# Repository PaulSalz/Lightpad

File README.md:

<div align="center">
<h1 align="center"><b>LightPad</b></h1>
DIY MIDI Controller to use with the Midi2LR Plugin

<picture>

</picture>
</div>
<br>

<picture>

</picture>

# Main features
- **[24x Interrupt-Driven Encoders](https://github.com/PaulSalz/lightpad/blob/main/Media/test_enc_led.jpg)**  
     - 3x8 RGB-illuminated Push-Button Encoders for all the main sliders, Lights, HSl, Details, ColorGrading, Effects...
- **[4x4 Button Matrix](https://github.com/PaulSalz/lightpad/blob/main/Media/top_view.jpg)**  
     - 16x RGB Buttons for easy Preset, Shortcut access
- **[Main Module](https://github.com/PaulSalz/lightpad/blob/main/Media/test_all.jpg)**  
     - 2x8 Buttons for switching Layers and often used features
- **[Media/ Culling Pad](https://github.com/PaulSalz/lightpad/blob/main/Media/side_view.jpg)**  
     - 8x RGB Buttons and an ANO Directional Navigation and Scroll Wheel to cull and navigate your library
- **[Force Feedback](https://github.com/PaulSalz/lightpad/blob/main/Media/test_all.jpg)**  
     - Integrated ERM Motor with DRV2605L for easy haptic effects 
- **[IR Remote Control](https://github.com/PaulSalz/lightpad/blob/main/Media/test_all.jpg)**  
     - Sometimes stepping back and cull from a distance helps me with culling
- **[Easy to print dual color case](https://www.rosa3d.pl/)**  
    - all printed from Rosa3D-Filaments PETG 
- **[Low/ High power mode](https://github.com/PaulSalz/lightpad/blob/main/Hardware/LightPad_BOM.html)**  
    - Full brightness gets unlocked with a external 5V source, and a mechanical switch on the main controller to prevent brown outs
- **[Animations]()**  
    - Idle animation
    - Button/ Encoder Effects
    - Backside illumination
- **[EL-Facts](https://github.com/PaulSalz/lightpad/blob/main/Media/usecase.jpg)**
    - Teensy 4.1 based
    - resettable fuses for both power inputs
    - RT1985N-A Protection IC for Softstart (needs some work)
    - I²C Level Shift 
    - Dual 74HC2G34 Buffer Gate for the LED's (using DMA)
    - expansion header for a Touch SPI Screen
    - all inputs connected through MCP23017 I/O expanders
  
<br>
<div align="center">
     
<picture>

</picture>
<picture>

</picture>
<picture>

</picture>
     
</div>
<br>

## TO-DO
  - fix all the bugs that occurred during assembly
  - rewrite the code so everything can be configured on the fly without reflashing
  - ...

## Background
- In the past I used a Behringer X-Touch mini for editing with Lightroom Classic and although this worked somewhat great enough to convince colleagues to also get one I wanted more, having to constantly switch layers, modes and remembering all of them to find the right settings annoyed me and gave me the motivation for this. 
  There are other great options out there but I wanted something without proprietary software that maybe gets bricked in the future. and i wanted something fancy, something completly over the top, do you need that many LED's? hell no..  But they definitely help a lot with remembering all the functions and look awesome.

## Disclaimer
- This is a first try on a DIY Midi controller that was created roughly in a span of a month from idea to actually getting used.  
- There will be and there are bugs, for example part of the pcb's need a bit of rework and changes to work out of the box.

<br>
<div align="center">
     
<picture>

</picture>
<picture>

</picture>
     
</div>
<br>

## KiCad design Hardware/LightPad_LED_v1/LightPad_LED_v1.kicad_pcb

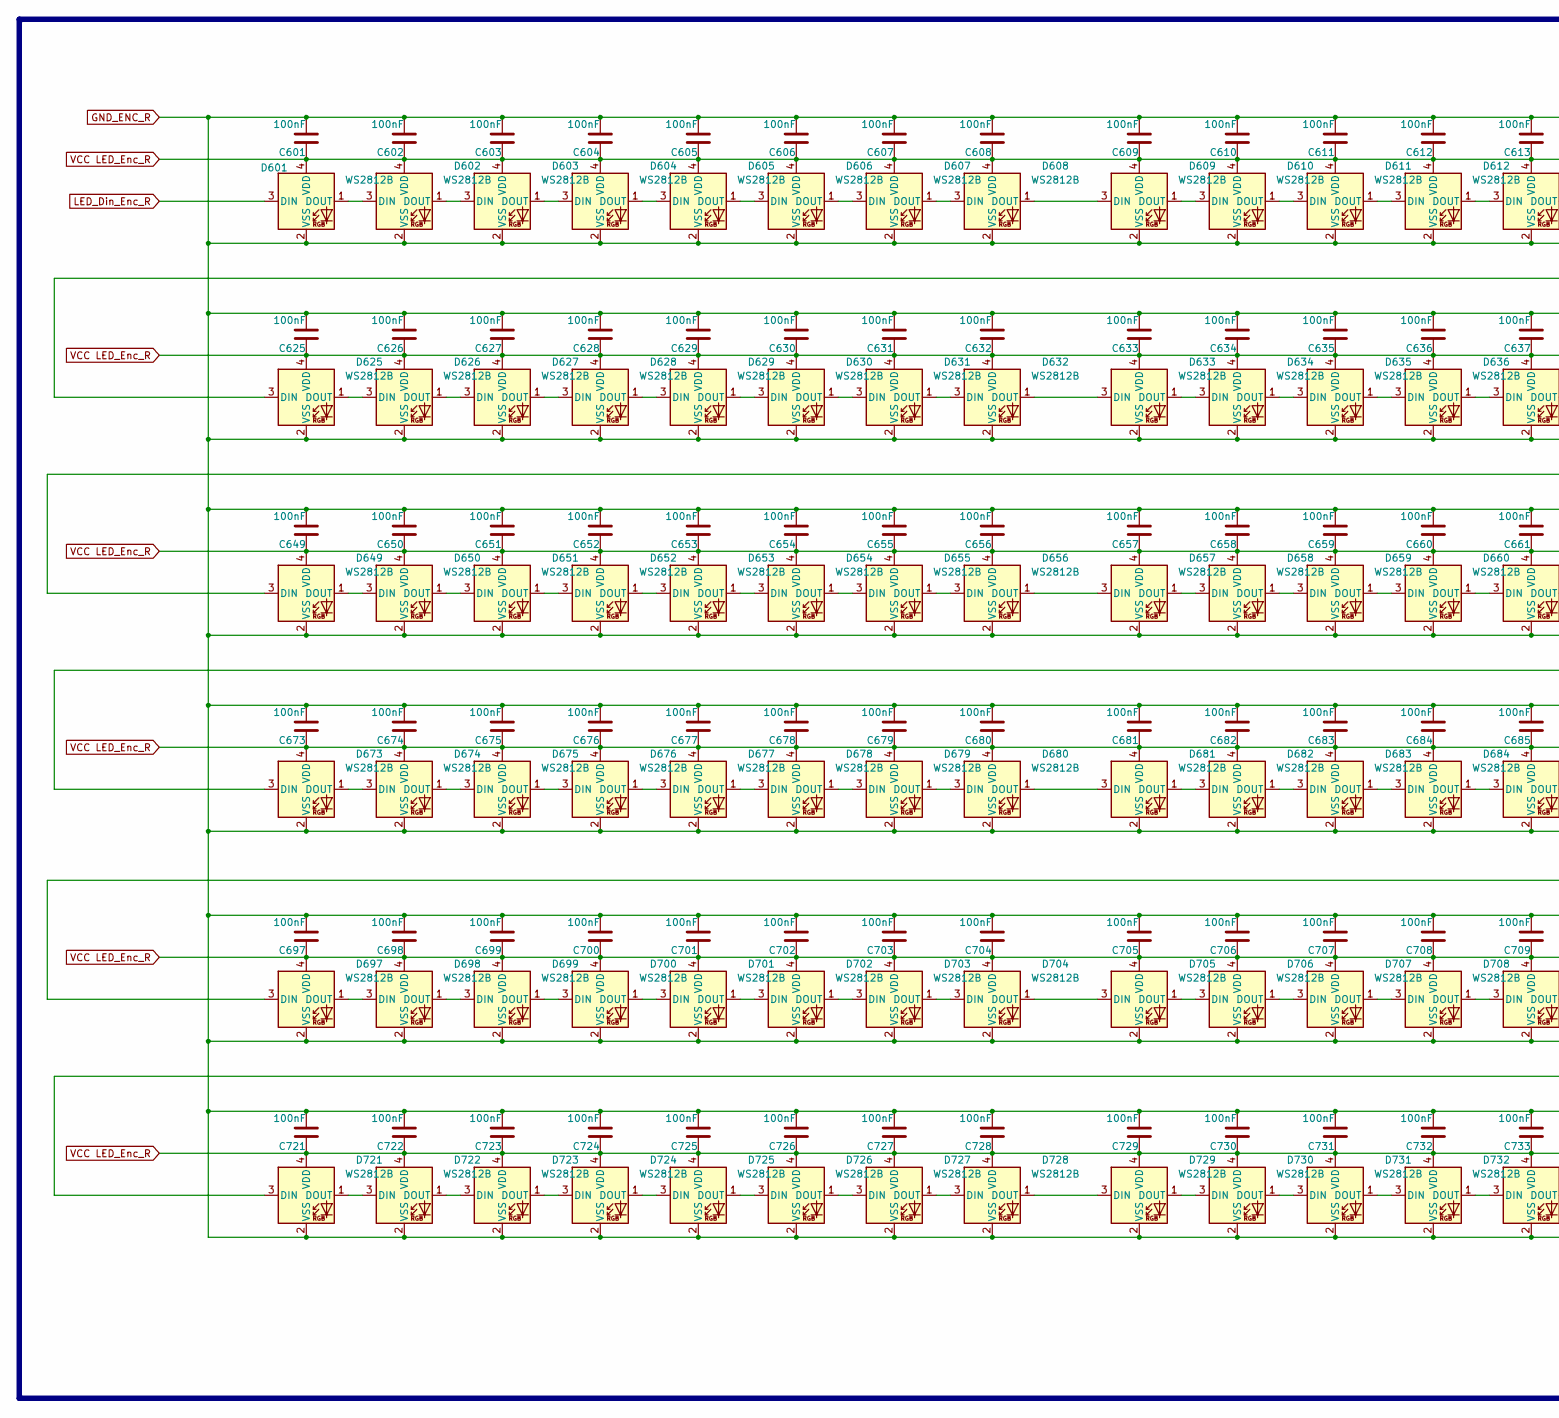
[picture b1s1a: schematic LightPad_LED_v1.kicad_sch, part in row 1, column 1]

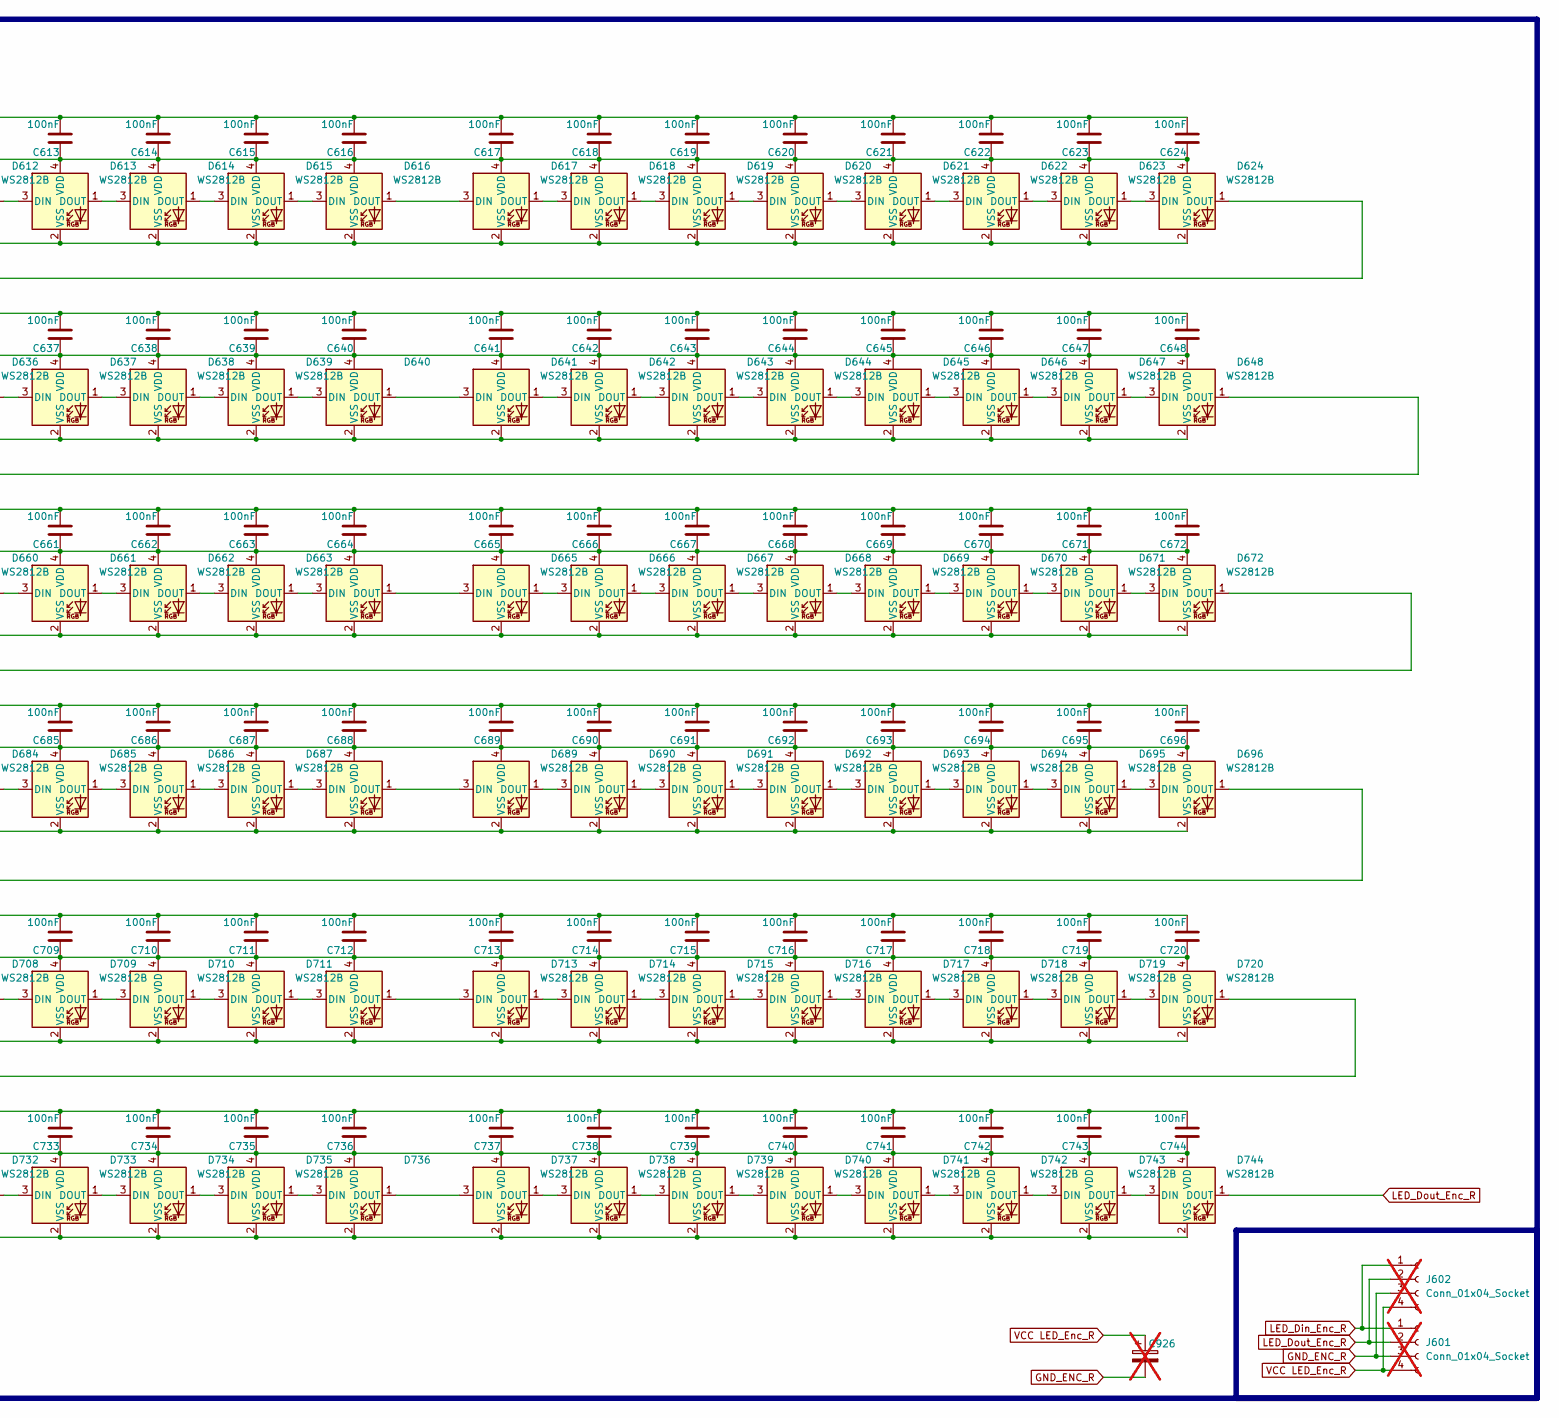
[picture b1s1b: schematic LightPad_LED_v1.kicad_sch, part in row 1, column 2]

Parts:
C601, C602, C603, C604, C605, C606, C607, C608, C609, C610, C611, C612, C613, C614, C615, C616, C617, C618, C619, C620, C621, C622, C623, C624, C625, C626, C627, C628, C629, C630, C631, C632, C633, C634, C635, C636, C637, C638, C639, C640, C641, C642, C643, C644, C645, C646, C647, C648, C649, C650, C651, C652, C653, C654, C655, C656, C657, C658, C659, C660, C661, C662, C663, C664, C665, C666, C667, C668, C669, C670, C671, C672, C673, C674, C675, C676, C677, C678, C679, C680, C681, C682, C683, C684, C685, C686, C687, C688, C689, C690, C691, C692, C693, C694, C695, C696, C697, C698, C699, C700, C701, C702, C703, C704, C705, C706, C707, C708, C709, C710, C711, C712, C713, C714, C715, C716, C717, C718, C719, C720, C721, C722, C723, C724, C725, C726, C727, C728, C729, C730, C731, C732, C733, C734, C735, C736, C737, C738, C739, C740, C741, C742, C743, C744: 100nF; C_0603_1608Metric; LCSC C24452
C926: APXE100ARA471MJ80G; C_Radial_D6.3mm_H5.0mm_P2.50mm; not fitted
D601, D602, D603, D604, D605, D606, D607, D608, D609, D610, D611, D612, D613, D614, D615, D616, D617, D618, D619, D620, D621, D622, D623, D624, D625, D626, D627, D628, D629, D630, D631, D632, D633, D634, D635, D636, D637, D638, D639, D640, D641, D642, D643, D644, D645, D646, D647, D648, D649, D650, D651, D652, D653, D654, D655, D656, D657, D658, D659, D660, D661, D662, D663, D664, D665, D666, D667, D668, D669, D670, D671, D672, D673, D674, D675, D676, D677, D678, D679, D680, D681, D682, D683, D684, D685, D686, D687, D688, D689, D690, D691, D692, D693, D694, D695, D696, D697, D698, D699, D700, D701, D702, D703, D704, D705, D706, D707, D708, D709, D710, D711, D712, D713, D714, D715, D716, D717, D718, D719, D720, D721, D722, D723, D724, D725, D726, D727, D728, D729, D730, D731, D732, D733, D734, D735, D736, D737, D738, D739, D740, D741, D742, D743, D744: WS2812B; LED_WS2812B-2020_PLCC4_2.0x2.0mm; LCSC C965555
J601, J602: Conn_01x04_Socket; PinSocket_1x04_P2.54mm_Vertical; not fitted

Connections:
GND_ENC_R: C601.1, C602.1, C603.1, C604.1, C605.1, C606.1, C607.1, C608.1, C609.1, C610.1, C611.1, C612.1, C613.1, C614.1, C615.1, C616.1, C617.1, C618.1, C619.1, C620.1, C621.1, C622.1, C623.1, C624.1, C625.1, C626.1, C627.1, C628.1, C629.1, C630.1, C631.1, C632.1, C633.1, C634.1, C635.1, C636.1, C637.1, C638.1, C639.1, C640.1, C641.1, C642.1, C643.1, C644.1, C645.1, C646.1, C647.1, C648.1, C649.1, C650.1, C651.1, C652.1, C653.1, C654.1, C655.1, C656.1, C657.1, C658.1, C659.1, C660.1, C661.1, C662.1, C663.1, C664.1, C665.1, C666.1, C667.1, C668.1, C669.1, C670.1, C671.1, C672.1, C673.1, C674.1, C675.1, C676.1, C677.1, C678.1, C679.1, C680.1, C681.1, C682.1, C683.1, C684.1, C685.1, C686.1, C687.1, C688.1, C689.1, C690.1, C691.1, C692.1, C693.1, C694.1, C695.1, C696.1, C697.1, C698.1, C699.1, C700.1, C701.1, C702.1, C703.1, C704.1, C705.1, C706.1, C707.1, C708.1, C709.1, C710.1, C711.1, C712.1, C713.1, C714.1, C715.1, C716.1, C717.1, C718.1, C719.1, C720.1, C721.1, C722.1, C723.1, C724.1, C725.1, C726.1, C727.1, C728.1, C729.1, C730.1, C731.1, C732.1, C733.1, C734.1, C735.1, C736.1, C737.1, C738.1, C739.1, C740.1, C741.1, C742.1, C743.1, C744.1, C926.2, D601.2 (VSS), D602.2 (VSS), D603.2 (VSS), D604.2 (VSS), D605.2 (VSS), D606.2 (VSS), D607.2 (VSS), D608.2 (VSS), D609.2 (VSS), D610.2 (VSS), D611.2 (VSS), D612.2 (VSS), D613.2 (VSS), D614.2 (VSS), D615.2 (VSS), D616.2 (VSS), D617.2 (VSS), D618.2 (VSS), D619.2 (VSS), D620.2 (VSS), D621.2 (VSS), D622.2 (VSS), D623.2 (VSS), D624.2 (VSS), D625.2 (VSS), D626.2 (VSS), D627.2 (VSS), D628.2 (VSS), D629.2 (VSS), D630.2 (VSS), D631.2 (VSS), D632.2 (VSS), D633.2 (VSS), D634.2 (VSS), D635.2 (VSS), D636.2 (VSS), D637.2 (VSS), D638.2 (VSS), D639.2 (VSS), D640.2 (VSS), D641.2 (VSS), D642.2 (VSS), D643.2 (VSS), D644.2 (VSS), D645.2 (VSS), D646.2 (VSS), D647.2 (VSS), D648.2 (VSS), D649.2 (VSS), D650.2 (VSS), D651.2 (VSS), D652.2 (VSS), D653.2 (VSS), D654.2 (VSS), D655.2 (VSS), D656.2 (VSS), D657.2 (VSS), D658.2 (VSS), D659.2 (VSS), D660.2 (VSS), D661.2 (VSS), D662.2 (VSS), D663.2 (VSS), D664.2 (VSS), D665.2 (VSS), D666.2 (VSS), D667.2 (VSS), D668.2 (VSS), D669.2 (VSS), D670.2 (VSS), D671.2 (VSS), D672.2 (VSS), D673.2 (VSS), D674.2 (VSS), D675.2 (VSS), D676.2 (VSS), D677.2 (VSS), D678.2 (VSS), D679.2 (VSS), D680.2 (VSS), D681.2 (VSS), D682.2 (VSS), D683.2 (VSS), D684.2 (VSS), D685.2 (VSS), D686.2 (VSS), D687.2 (VSS), D688.2 (VSS), D689.2 (VSS), D690.2 (VSS), D691.2 (VSS), D692.2 (VSS), D693.2 (VSS), D694.2 (VSS), D695.2 (VSS), D696.2 (VSS), D697.2 (VSS), D698.2 (VSS), D699.2 (VSS), D700.2 (VSS), D701.2 (VSS), D702.2 (VSS), D703.2 (VSS), D704.2 (VSS), D705.2 (VSS), D706.2 (VSS), D707.2 (VSS), D708.2 (VSS), D709.2 (VSS), D710.2 (VSS), D711.2 (VSS), D712.2 (VSS), D713.2 (VSS), D714.2 (VSS), D715.2 (VSS), D716.2 (VSS), D717.2 (VSS), D718.2 (VSS), D719.2 (VSS), D720.2 (VSS), D721.2 (VSS), D722.2 (VSS), D723.2 (VSS), D724.2 (VSS), D725.2 (VSS), D726.2 (VSS), D727.2 (VSS), D728.2 (VSS), D729.2 (VSS), D730.2 (VSS), D731.2 (VSS), D732.2 (VSS), D733.2 (VSS), D734.2 (VSS), D735.2 (VSS), D736.2 (VSS), D737.2 (VSS), D738.2 (VSS), D739.2 (VSS), D740.2 (VSS), D741.2 (VSS), D742.2 (VSS), D743.2 (VSS), D744.2 (VSS), J601.3, J602.3
LED_Din_Enc_R: D601.3 (DIN), J601.1, J602.1
LED_Dout_Enc_R: D744.1 (DOUT), J601.2, J602.2
unnamed: D601.1 (DOUT), D602.3 (DIN)
unnamed: D602.1 (DOUT), D603.3 (DIN)
unnamed: D603.1 (DOUT), D604.3 (DIN)
unnamed: D604.1 (DOUT), D605.3 (DIN)
unnamed: D605.1 (DOUT), D606.3 (DIN)
unnamed: D606.1 (DOUT), D607.3 (DIN)
unnamed: D607.1 (DOUT), D608.3 (DIN)
unnamed: D608.1 (DOUT), D609.3 (DIN)
unnamed: D609.1 (DOUT), D610.3 (DIN)
unnamed: D610.1 (DOUT), D611.3 (DIN)
unnamed: D611.1 (DOUT), D612.3 (DIN)
unnamed: D612.1 (DOUT), D613.3 (DIN)
unnamed: D613.1 (DOUT), D614.3 (DIN)
unnamed: D614.1 (DOUT), D615.3 (DIN)
unnamed: D615.1 (DOUT), D616.3 (DIN)
unnamed: D616.1 (DOUT), D617.3 (DIN)
unnamed: D617.1 (DOUT), D618.3 (DIN)
unnamed: D618.1 (DOUT), D619.3 (DIN)
unnamed: D619.1 (DOUT), D620.3 (DIN)
unnamed: D620.1 (DOUT), D621.3 (DIN)
unnamed: D621.1 (DOUT), D622.3 (DIN)
unnamed: D622.1 (DOUT), D623.3 (DIN)
unnamed: D623.1 (DOUT), D624.3 (DIN)
unnamed: D624.1 (DOUT), D625.3 (DIN)
unnamed: D625.1 (DOUT), D626.3 (DIN)
unnamed: D626.1 (DOUT), D627.3 (DIN)
unnamed: D627.1 (DOUT), D628.3 (DIN)
unnamed: D628.1 (DOUT), D629.3 (DIN)
unnamed: D629.1 (DOUT), D630.3 (DIN)
unnamed: D630.1 (DOUT), D631.3 (DIN)
unnamed: D631.1 (DOUT), D632.3 (DIN)
unnamed: D632.1 (DOUT), D633.3 (DIN)
unnamed: D633.1 (DOUT), D634.3 (DIN)
unnamed: D634.1 (DOUT), D635.3 (DIN)
unnamed: D635.1 (DOUT), D636.3 (DIN)
unnamed: D636.1 (DOUT), D637.3 (DIN)
unnamed: D637.1 (DOUT), D638.3 (DIN)
unnamed: D638.1 (DOUT), D639.3 (DIN)
unnamed: D639.1 (DOUT), D640.3 (DIN)
unnamed: D640.1 (DOUT), D641.3 (DIN)
unnamed: D641.1 (DOUT), D642.3 (DIN)
unnamed: D642.1 (DOUT), D643.3 (DIN)
unnamed: D643.1 (DOUT), D644.3 (DIN)
unnamed: D644.1 (DOUT), D645.3 (DIN)
unnamed: D645.1 (DOUT), D646.3 (DIN)
unnamed: D646.1 (DOUT), D647.3 (DIN)
unnamed: D647.1 (DOUT), D648.3 (DIN)
unnamed: D648.1 (DOUT), D649.3 (DIN)
unnamed: D649.1 (DOUT), D650.3 (DIN)
unnamed: D650.1 (DOUT), D651.3 (DIN)
unnamed: D651.1 (DOUT), D652.3 (DIN)
unnamed: D652.1 (DOUT), D653.3 (DIN)
unnamed: D653.1 (DOUT), D654.3 (DIN)
unnamed: D654.1 (DOUT), D655.3 (DIN)
unnamed: D655.1 (DOUT), D656.3 (DIN)
unnamed: D656.1 (DOUT), D657.3 (DIN)
unnamed: D657.1 (DOUT), D658.3 (DIN)
unnamed: D658.1 (DOUT), D659.3 (DIN)
unnamed: D659.1 (DOUT), D660.3 (DIN)
unnamed: D660.1 (DOUT), D661.3 (DIN)
unnamed: D661.1 (DOUT), D662.3 (DIN)
unnamed: D662.1 (DOUT), D663.3 (DIN)
unnamed: D663.1 (DOUT), D664.3 (DIN)
unnamed: D664.1 (DOUT), D665.3 (DIN)
unnamed: D665.1 (DOUT), D666.3 (DIN)
unnamed: D666.1 (DOUT), D667.3 (DIN)
unnamed: D667.1 (DOUT), D668.3 (DIN)
unnamed: D668.1 (DOUT), D669.3 (DIN)
unnamed: D669.1 (DOUT), D670.3 (DIN)
unnamed: D670.1 (DOUT), D671.3 (DIN)
unnamed: D671.1 (DOUT), D672.3 (DIN)
unnamed: D672.1 (DOUT), D673.3 (DIN)
unnamed: D673.1 (DOUT), D674.3 (DIN)
unnamed: D674.1 (DOUT), D675.3 (DIN)
unnamed: D675.1 (DOUT), D676.3 (DIN)
unnamed: D676.1 (DOUT), D677.3 (DIN)
unnamed: D677.1 (DOUT), D678.3 (DIN)
unnamed: D678.1 (DOUT), D679.3 (DIN)
unnamed: D679.1 (DOUT), D680.3 (DIN)
unnamed: D680.1 (DOUT), D681.3 (DIN)
unnamed: D681.1 (DOUT), D682.3 (DIN)
unnamed: D682.1 (DOUT), D683.3 (DIN)
unnamed: D683.1 (DOUT), D684.3 (DIN)
unnamed: D684.1 (DOUT), D685.3 (DIN)
unnamed: D685.1 (DOUT), D686.3 (DIN)
unnamed: D686.1 (DOUT), D687.3 (DIN)
unnamed: D687.1 (DOUT), D688.3 (DIN)
unnamed: D688.1 (DOUT), D689.3 (DIN)
unnamed: D689.1 (DOUT), D690.3 (DIN)
unnamed: D690.1 (DOUT), D691.3 (DIN)
unnamed: D691.1 (DOUT), D692.3 (DIN)
unnamed: D692.1 (DOUT), D693.3 (DIN)
unnamed: D693.1 (DOUT), D694.3 (DIN)
unnamed: D694.1 (DOUT), D695.3 (DIN)
unnamed: D695.1 (DOUT), D696.3 (DIN)
unnamed: D696.1 (DOUT), D697.3 (DIN)
unnamed: D697.1 (DOUT), D698.3 (DIN)
unnamed: D698.1 (DOUT), D699.3 (DIN)
unnamed: D699.1 (DOUT), D700.3 (DIN)
unnamed: D700.1 (DOUT), D701.3 (DIN)
unnamed: D701.1 (DOUT), D702.3 (DIN)
unnamed: D702.1 (DOUT), D703.3 (DIN)
unnamed: D703.1 (DOUT), D704.3 (DIN)
unnamed: D704.1 (DOUT), D705.3 (DIN)
unnamed: D705.1 (DOUT), D706.3 (DIN)
unnamed: D706.1 (DOUT), D707.3 (DIN)
unnamed: D707.1 (DOUT), D708.3 (DIN)
unnamed: D708.1 (DOUT), D709.3 (DIN)
unnamed: D709.1 (DOUT), D710.3 (DIN)
unnamed: D710.1 (DOUT), D711.3 (DIN)
unnamed: D711.1 (DOUT), D712.3 (DIN)
unnamed: D712.1 (DOUT), D713.3 (DIN)
unnamed: D713.1 (DOUT), D714.3 (DIN)
unnamed: D714.1 (DOUT), D715.3 (DIN)
unnamed: D715.1 (DOUT), D716.3 (DIN)
unnamed: D716.1 (DOUT), D717.3 (DIN)
unnamed: D717.1 (DOUT), D718.3 (DIN)
unnamed: D718.1 (DOUT), D719.3 (DIN)
unnamed: D719.1 (DOUT), D720.3 (DIN)
unnamed: D720.1 (DOUT), D721.3 (DIN)
unnamed: D721.1 (DOUT), D722.3 (DIN)
unnamed: D722.1 (DOUT), D723.3 (DIN)
unnamed: D723.1 (DOUT), D724.3 (DIN)
unnamed: D724.1 (DOUT), D725.3 (DIN)
unnamed: D725.1 (DOUT), D726.3 (DIN)
unnamed: D726.1 (DOUT), D727.3 (DIN)
unnamed: D727.1 (DOUT), D728.3 (DIN)
unnamed: D728.1 (DOUT), D729.3 (DIN)
unnamed: D729.1 (DOUT), D730.3 (DIN)
unnamed: D730.1 (DOUT), D731.3 (DIN)
unnamed: D731.1 (DOUT), D732.3 (DIN)
unnamed: D732.1 (DOUT), D733.3 (DIN)
unnamed: D733.1 (DOUT), D734.3 (DIN)
unnamed: D734.1 (DOUT), D735.3 (DIN)
unnamed: D735.1 (DOUT), D736.3 (DIN)
unnamed: D736.1 (DOUT), D737.3 (DIN)
unnamed: D737.1 (DOUT), D738.3 (DIN)
unnamed: D738.1 (DOUT), D739.3 (DIN)
unnamed: D739.1 (DOUT), D740.3 (DIN)
unnamed: D740.1 (DOUT), D741.3 (DIN)
unnamed: D741.1 (DOUT), D742.3 (DIN)
unnamed: D742.1 (DOUT), D743.3 (DIN)
unnamed: D743.1 (DOUT), D744.3 (DIN)
VCC LED_Enc_R: C601.2, C602.2, C603.2, C604.2, C605.2, C606.2, C607.2, C608.2, C609.2, C610.2, C611.2, C612.2, C613.2, C614.2, C615.2, C616.2, C617.2, C618.2, C619.2, C620.2, C621.2, C622.2, C623.2, C624.2, C625.2, C626.2, C627.2, C628.2, C629.2, C630.2, C631.2, C632.2, C633.2, C634.2, C635.2, C636.2, C637.2, C638.2, C639.2, C640.2, C641.2, C642.2, C643.2, C644.2, C645.2, C646.2, C647.2, C648.2, C649.2, C650.2, C651.2, C652.2, C653.2, C654.2, C655.2, C656.2, C657.2, C658.2, C659.2, C660.2, C661.2, C662.2, C663.2, C664.2, C665.2, C666.2, C667.2, C668.2, C669.2, C670.2, C671.2, C672.2, C673.2, C674.2, C675.2, C676.2, C677.2, C678.2, C679.2, C680.2, C681.2, C682.2, C683.2, C684.2, C685.2, C686.2, C687.2, C688.2, C689.2, C690.2, C691.2, C692.2, C693.2, C694.2, C695.2, C696.2, C697.2, C698.2, C699.2, C700.2, C701.2, C702.2, C703.2, C704.2, C705.2, C706.2, C707.2, C708.2, C709.2, C710.2, C711.2, C712.2, C713.2, C714.2, C715.2, C716.2, C717.2, C718.2, C719.2, C720.2, C721.2, C722.2, C723.2, C724.2, C725.2, C726.2, C727.2, C728.2, C729.2, C730.2, C731.2, C732.2, C733.2, C734.2, C735.2, C736.2, C737.2, C738.2, C739.2, C740.2, C741.2, C742.2, C743.2, C744.2, C926.1, D601.4 (VDD), D602.4 (VDD), D603.4 (VDD), D604.4 (VDD), D605.4 (VDD), D606.4 (VDD), D607.4 (VDD), D608.4 (VDD), D609.4 (VDD), D610.4 (VDD), D611.4 (VDD), D612.4 (VDD), D613.4 (VDD), D614.4 (VDD), D615.4 (VDD), D616.4 (VDD), D617.4 (VDD), D618.4 (VDD), D619.4 (VDD), D620.4 (VDD), D621.4 (VDD), D622.4 (VDD), D623.4 (VDD), D624.4 (VDD), D625.4 (VDD), D626.4 (VDD), D627.4 (VDD), D628.4 (VDD), D629.4 (VDD), D630.4 (VDD), D631.4 (VDD), D632.4 (VDD), D633.4 (VDD), D634.4 (VDD), D635.4 (VDD), D636.4 (VDD), D637.4 (VDD), D638.4 (VDD), D639.4 (VDD), D640.4 (VDD), D641.4 (VDD), D642.4 (VDD), D643.4 (VDD), D644.4 (VDD), D645.4 (VDD), D646.4 (VDD), D647.4 (VDD), D648.4 (VDD), D649.4 (VDD), D650.4 (VDD), D651.4 (VDD), D652.4 (VDD), D653.4 (VDD), D654.4 (VDD), D655.4 (VDD), D656.4 (VDD), D657.4 (VDD), D658.4 (VDD), D659.4 (VDD), D660.4 (VDD), D661.4 (VDD), D662.4 (VDD), D663.4 (VDD), D664.4 (VDD), D665.4 (VDD), D666.4 (VDD), D667.4 (VDD), D668.4 (VDD), D669.4 (VDD), D670.4 (VDD), D671.4 (VDD), D672.4 (VDD), D673.4 (VDD), D674.4 (VDD), D675.4 (VDD), D676.4 (VDD), D677.4 (VDD), D678.4 (VDD), D679.4 (VDD), D680.4 (VDD), D681.4 (VDD), D682.4 (VDD), D683.4 (VDD), D684.4 (VDD), D685.4 (VDD), D686.4 (VDD), D687.4 (VDD), D688.4 (VDD), D689.4 (VDD), D690.4 (VDD), D691.4 (VDD), D692.4 (VDD), D693.4 (VDD), D694.4 (VDD), D695.4 (VDD), D696.4 (VDD), D697.4 (VDD), D698.4 (VDD), D699.4 (VDD), D700.4 (VDD), D701.4 (VDD), D702.4 (VDD), D703.4 (VDD), D704.4 (VDD), D705.4 (VDD), D706.4 (VDD), D707.4 (VDD), D708.4 (VDD), D709.4 (VDD), D710.4 (VDD), D711.4 (VDD), D712.4 (VDD), D713.4 (VDD), D714.4 (VDD), D715.4 (VDD), D716.4 (VDD), D717.4 (VDD), D718.4 (VDD), D719.4 (VDD), D720.4 (VDD), D721.4 (VDD), D722.4 (VDD), D723.4 (VDD), D724.4 (VDD), D725.4 (VDD), D726.4 (VDD), D727.4 (VDD), D728.4 (VDD), D729.4 (VDD), D730.4 (VDD), D731.4 (VDD), D732.4 (VDD), D733.4 (VDD), D734.4 (VDD), D735.4 (VDD), D736.4 (VDD), D737.4 (VDD), D738.4 (VDD), D739.4 (VDD), D740.4 (VDD), D741.4 (VDD), D742.4 (VDD), D743.4 (VDD), D744.4 (VDD), J601.4, J602.4

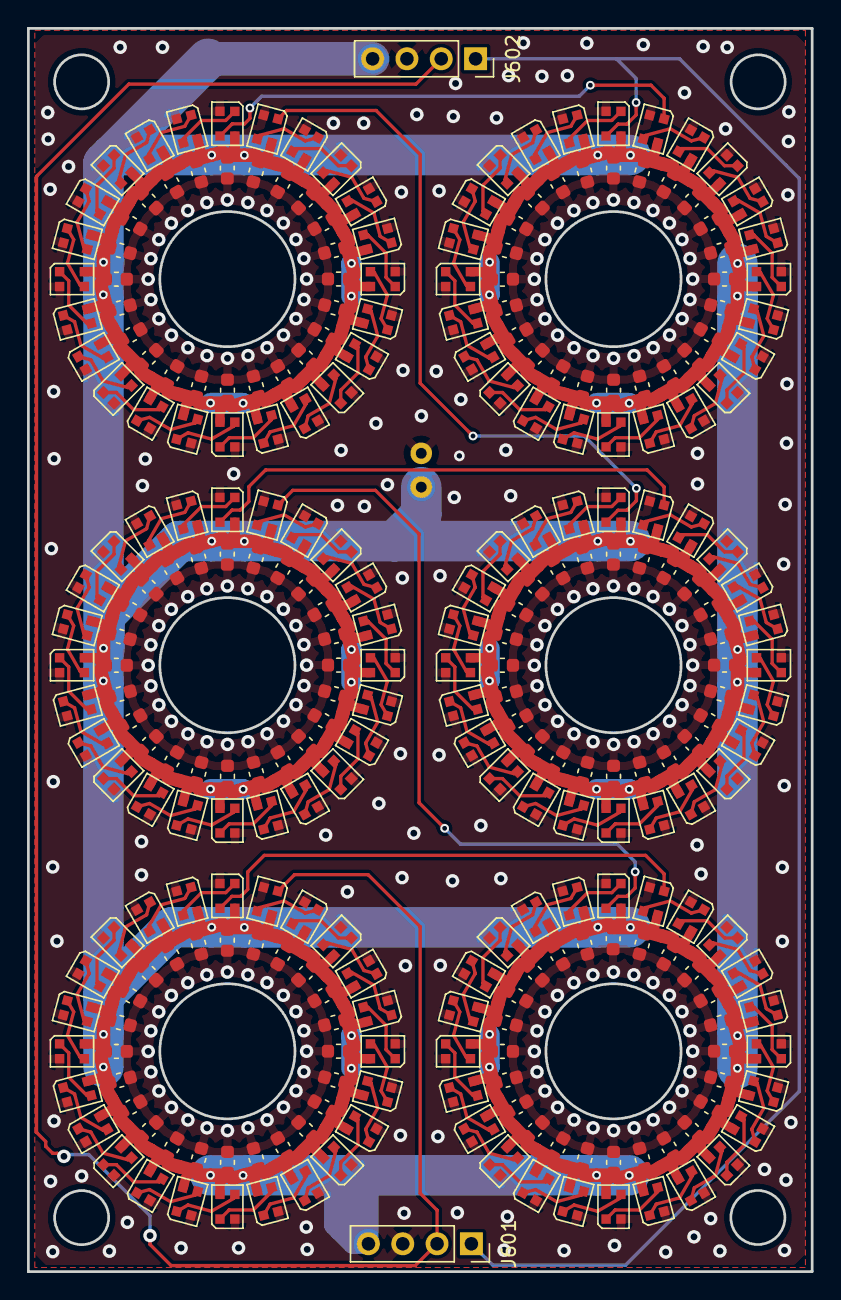
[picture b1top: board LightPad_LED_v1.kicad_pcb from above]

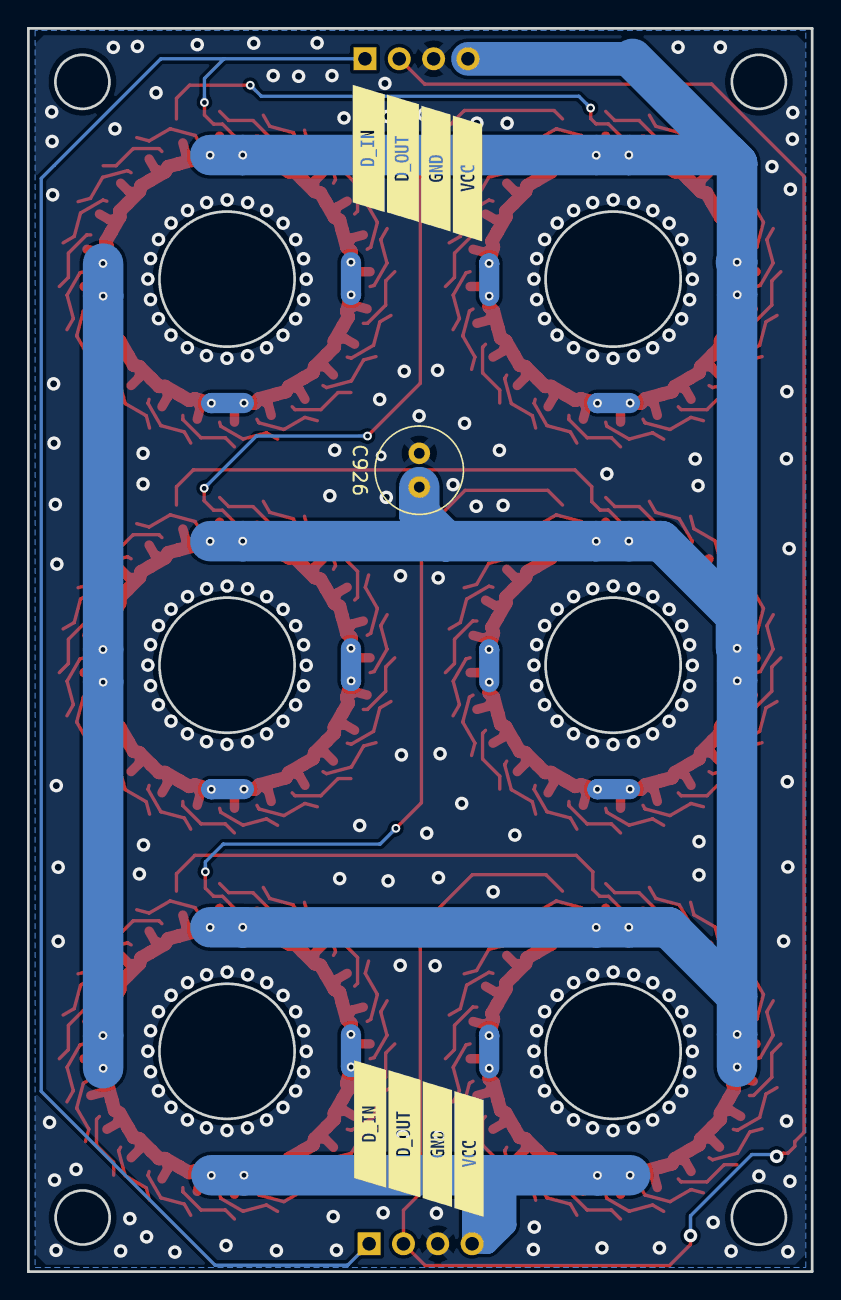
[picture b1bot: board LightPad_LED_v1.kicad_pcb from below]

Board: 2 copper layers, 58.0 x 92.0 mm, 299 parts (9 on the bottom side), 147 nets.

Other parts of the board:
kibuzzard-6880EE7E, kibuzzard-6880EE7E#2: G***; kibuzzard-6880EE7E
kibuzzard-6880EE9A, kibuzzard-6880EE9A#2: G***; kibuzzard-6880EE9A
kibuzzard-6880EEC9, kibuzzard-6880EEC9#2: G***; kibuzzard-6880EEC9
kibuzzard-6880EEE5, kibuzzard-6880EEE5#2: G***; kibuzzard-6880EEE5

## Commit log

2026-03-05 make git neat
2026-03-06 BOM added
2026-03-06 Revise README
    Updated features and background information for LightPad.
2026-03-06 Enhance README
    Updated README.md with new features, images, and links.
2026-03-06 Revise README with new content and images
    Updated README to include new features, images, and background information.
2026-03-09 update logo
2026-03-09 Add MIT License to the project
